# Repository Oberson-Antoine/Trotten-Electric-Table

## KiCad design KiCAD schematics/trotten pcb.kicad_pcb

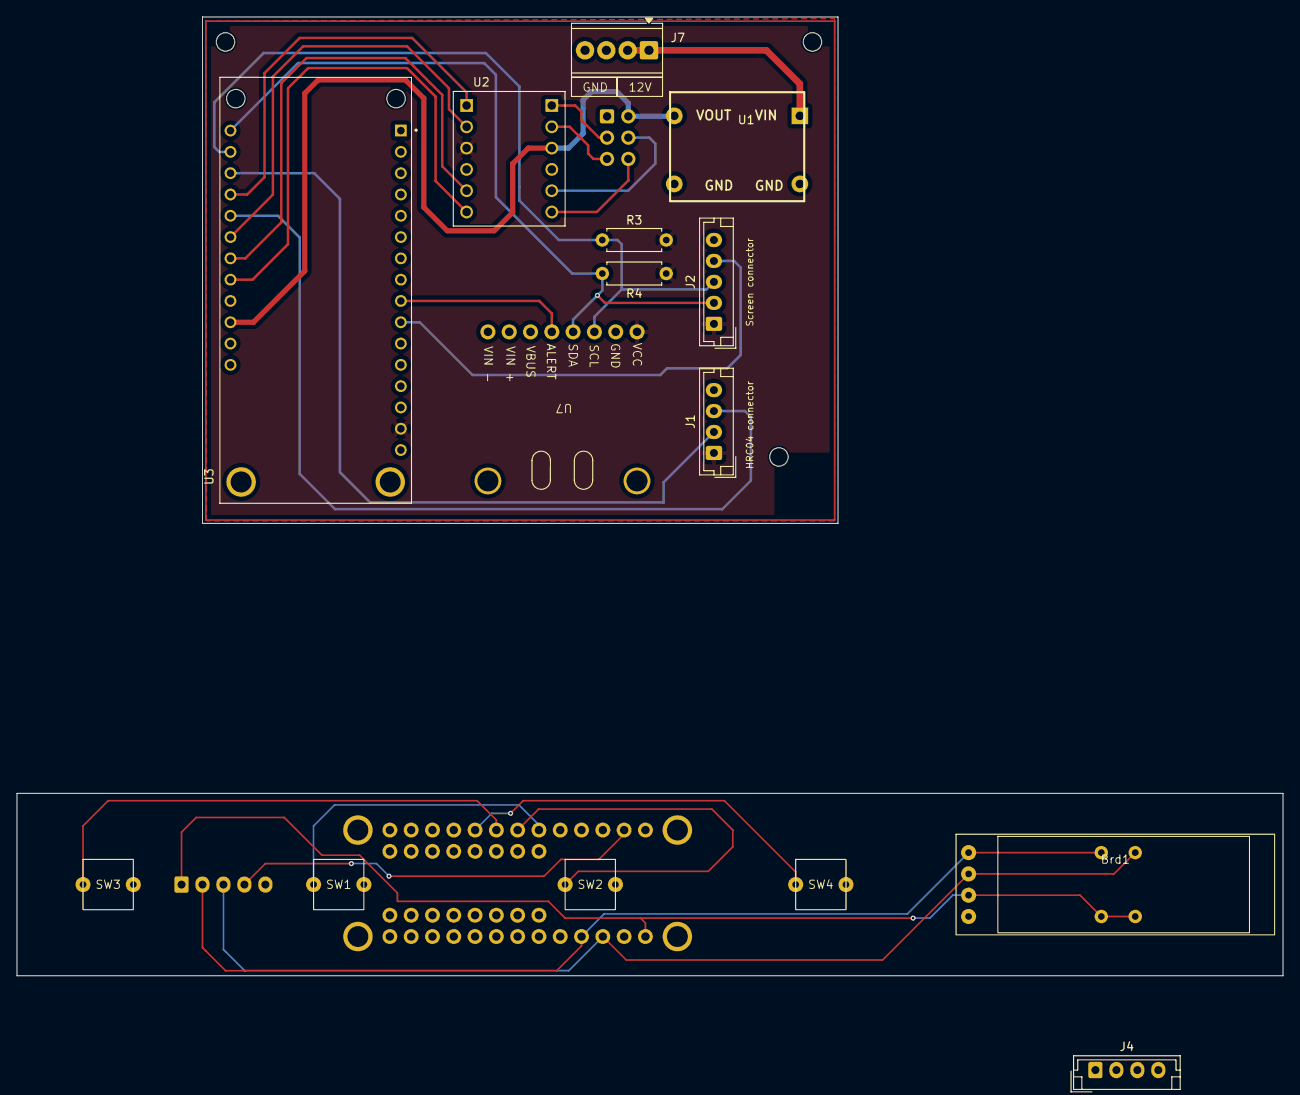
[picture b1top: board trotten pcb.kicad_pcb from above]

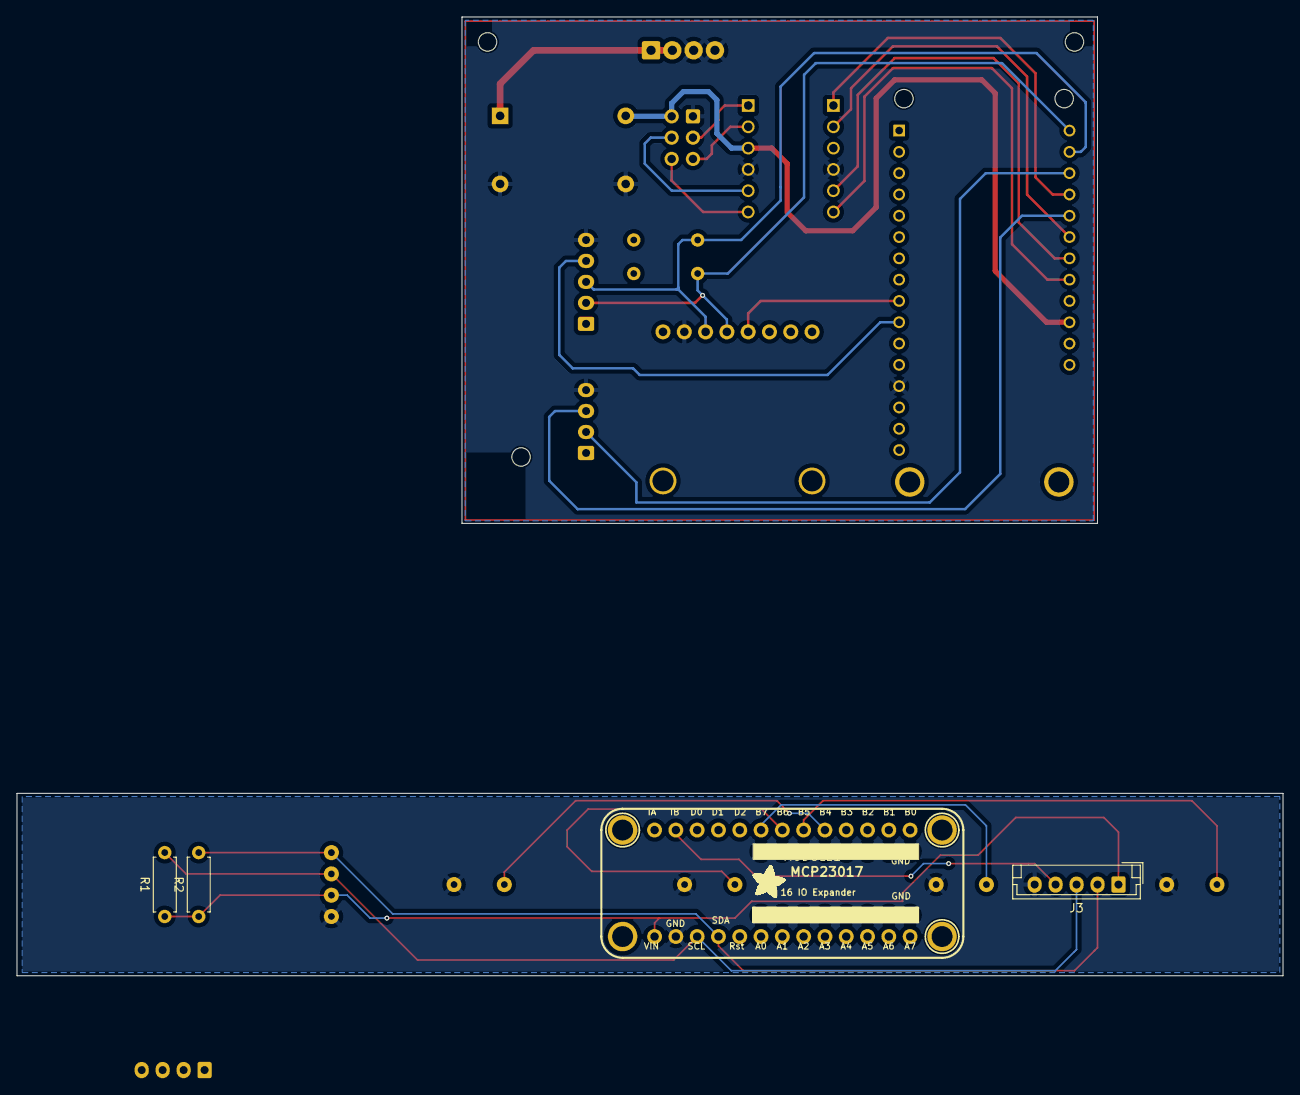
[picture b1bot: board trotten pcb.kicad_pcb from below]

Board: 2 copper layers, 151.0 x 114.3 mm, 20 parts (4 on the bottom side), 25 nets.

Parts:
Brd1: SSD1306
J1: Conn_HRCU4_main; JST_EH_B4B-EH-A_1x04_P2.50mm_Vertical
J2: Conn_screen_BRD_main; JST_EH_B5B-EH-A_1x05_P2.50mm_Vertical
J3: Conn_screen_BRD_Slave; JST_EH_B5B-EH-A_1x05_P2.50mm_Vertical
J4: Conn_01x04_Socket; JST_EH_B4B-EH-A_1x04_P2.50mm_Vertical
J5: Conn_02x03_Odd_Even; Connecteur_Moteur
J7: Screw_Terminal_01x04; TerminalBlock_Phoenix_MPT-0,5-4-2.54_1x04_P2.54mm_Horizontal
MODULE1: CJMCU-2317_MCP23017; MCP23017_ADAFRUIT
R1, R2, R3, R4: 10k; R_Axial_DIN0207_L6.3mm_D2.5mm_P7.62mm_Horizontal
SW1: Haut; 6x6x5_Button
SW2: Bas; 6x6x5_Button
SW3: MEM_1; 6x6x5_Button
SW4: MEM_2; 6x6x5_Button
U1: S09-EY9-DC-DC
U2: BOB-12009; CONV_BOB-12009
U3: ADAFRUIT-ESP32-S3; MODULE_3405
U7: INA260

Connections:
+3.3V: Brd1.2 (VCC), J1.1, J2.1, J3.1, MODULE1.30 (VCC), R1.1, R2.1, R3.2, R4.2, U2.LV, U3.15 (3V), U7.10 (VS)
+5V: J5.5, U1.3 (OUT), U2.HV, U3.19 (VBUS)
+12V: J7.1, J7.2, U1.1 (IN)
ECHO - D15: J1.3, U3.24 (A8/IO15)
GND: Brd1.1 (GND), J1.4, J2.5, J3.5, J5.6, J7.3, J7.4, MODULE1.29 (GND), SW1.2, SW2.2, SW3.2, SW4.2, U1.2 (GND), U1.4 (GND), U2.GND_1 (GND), U2.GND_2 (GND), U3.13 (GND), U7.6 (GND)
INT B - GP34: J2.4, U3.10 (A2/IO34)
INT CUR - GP39: U3.9 (A3/IO39), U7.7 (ALERT)
L-EN: U2.LV1, U3.25 (A7/IO32)
L-PWM: U2.LV2, U3.23 (A9/IO33)
unnamed: Brd1.3 (SCL), J3.3, MODULE1.28 (SCL/SCK), R1.2
unnamed: Brd1.4 (SDA), J3.2, MODULE1.27 (SDA/SI), R2.2
unnamed: J3.4, MODULE1.12 (ITB)
unnamed: J5.1, U2.HV4
unnamed: J5.2, U2.HV2
unnamed: J5.3, U2.HV3
unnamed: J5.4, U2.HV1
unnamed: MODULE1.17 (B4), SW4.1
unnamed: MODULE1.18 (B5), SW3.1
unnamed: MODULE1.19 (B6), SW2.1
unnamed: MODULE1.20 (B7), SW1.1
R-EN: U2.LV3, U3.22 (A10/IO27)
R-PWM: U2.LV4, U3.21 (A11/IO12)
SCL - GP22: J2.3, R3.1, U3.27 (SCL/IO22), U7.9 (SCL)
SDA - GPI 23: J2.2, R4.1, U3.28 (SDA/IO23), U7.8 (SDA)
TRIG - D14: J1.2, U3.26 (A6/IO14)

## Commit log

2025-06-22 advancing the kicad for the new esp, dev stalled
2025-06-26 SSD1306 working on esp32 s3
2025-06-28 Screen and ultrasound sensor working
2025-07-14 Contrast gestion done
2025-07-21 avancement PCB et 3d files
2025-08-07 avancé INA260
2025-08-26 commencé le moteur
